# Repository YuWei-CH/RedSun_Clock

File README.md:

# RedSun_Clock
RedSun_Clock is a PCB-based clock that I designed and developed independently. The project was guided by Mr.Ethan and Mr.Matthew during the Google Hardware Product Sprint (HPS2022 Summer). 

This project consists of two main parts: Hardware and Software.

## Hardware
The hardware part includes the design of the circuit board and the bill of materials (BOM).
Essential components:
LED Matrix  
Micro-controller(atmega328)  
Quartz crystal unit  
Printed Circuit Board  

## Software
The software part is composed of code written in Arduino, which drives the operation of the hardware. And I use KiCAD for PCB design and verification.

## How to compile the code
You can use the Arduino compiler to compile this code.

## Picture

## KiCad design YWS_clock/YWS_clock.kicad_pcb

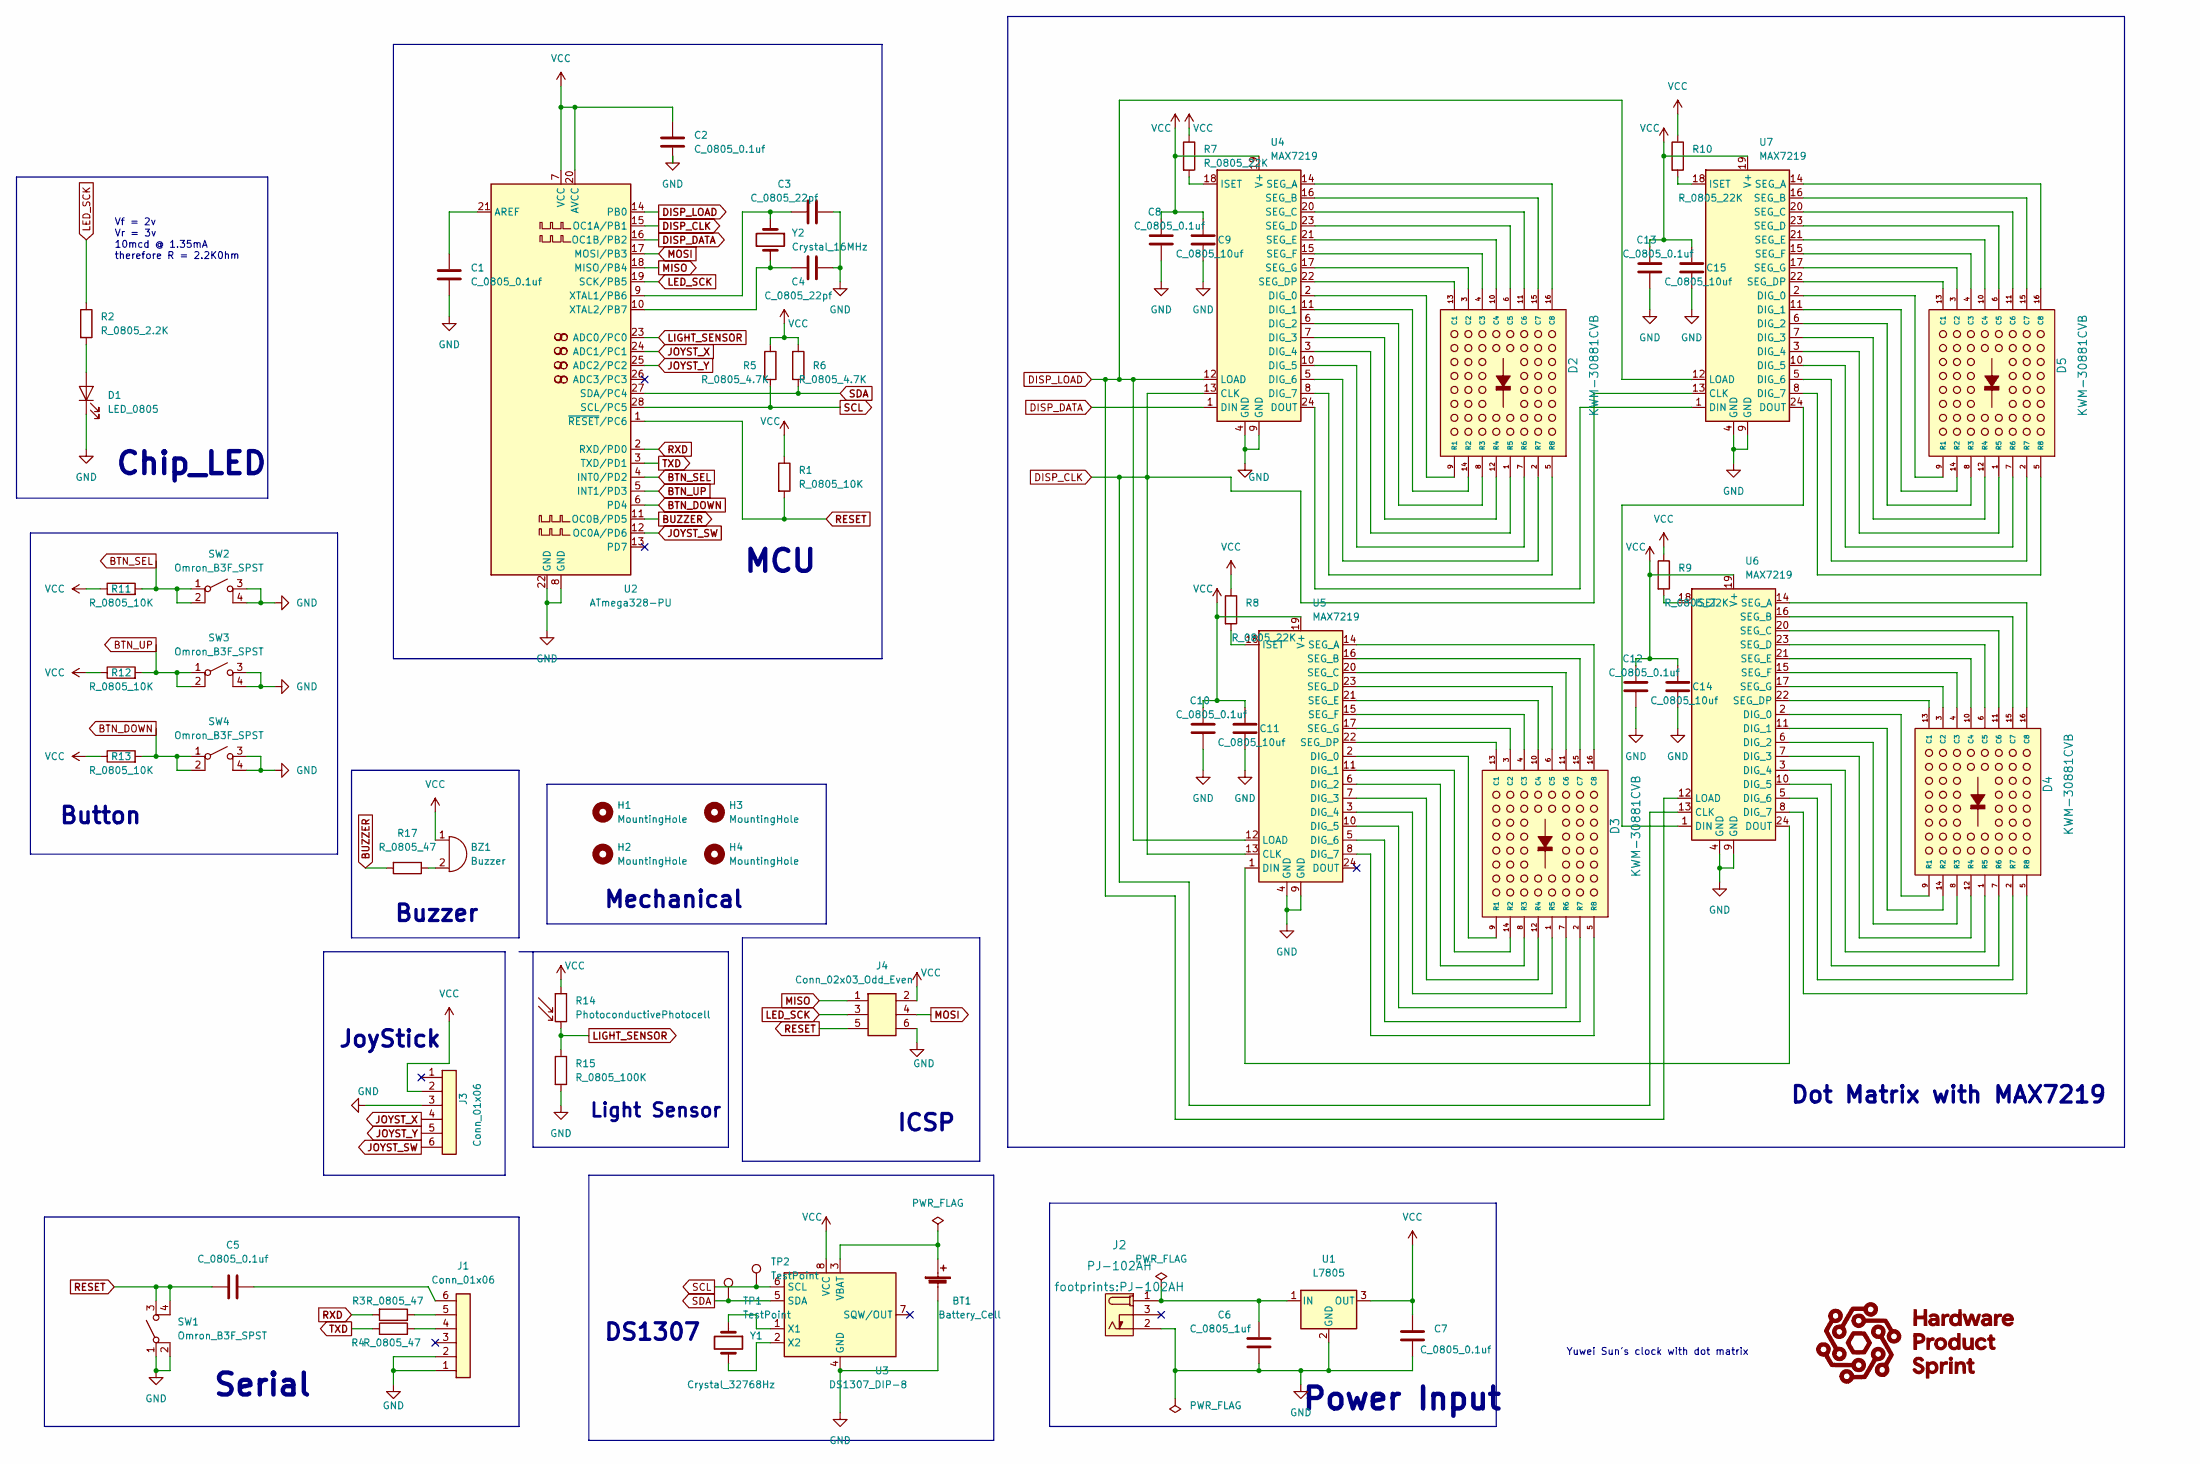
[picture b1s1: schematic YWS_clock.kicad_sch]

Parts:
BT1: Battery_Cell; BatteryHolder_Keystone_106_1x20mm; MPN BS-7; Digikey PN BS-7-ND
BZ1: Buzzer; Buzzer_TDK_PS1240P02BT_D12.2mm_H6.5mm; MPN PS1420P02CT; Digikey PN 445-2526-1-ND
C1, C2, C5, C7, C8, C10, C12, C13: C_0805_0.1uf; C_0805_2012Metric; Voltage N/A; Tolerance N/A; MPN 08055C104KAT2A; Digikey PN 478-1395-1-ND
C3, C4: C_0805_22pf; C_0805_2012Metric; Voltage N/A; Tolerance N/A; MPN CC0805JRNPO9BN220; Digikey PN 311-1103-1-ND
C6: C_0805_1uf; C_0805_2012Metric; Voltage N/A; Tolerance N/A; MPN CC0805KKX7R8BB105; Digikey PN 311-1456-1-ND
C9, C11, C14, C15: C_0805_10uf; C_0805_2012Metric; Voltage N/A; Tolerance N/A; MPN GRM21BR61E106KA73L; Digikey PN 490-5523-1-ND
D1: LED_0805; LED_0805_2012Metric; MPN 150080RS75000; Digikey PN 732-4984-1-ND
D2, D3, D4, D5: KWM-30881CVB; MPN KWM-30881CVB; Digikey PN N/A
H1, H2, H3, H4: MountingHole; MountingHole_3.2mm_M3
J1, J3: Conn_01x06; PinHeader_1x06_P2.54mm_Vertical; MPN 61300611121; Digikey PN 732-5319-ND
J2: PJ-102AH; MPN PJ-102AH; Digikey PN CP-102AH-ND
J4: Conn_02x03_Odd_Even; PinHeader_2x03_P2.54mm_Vertical; MPN PRPC003DAAN-RC; Digikey PN S2011EC-03-ND
R1, R11, R12, R13: R_0805_10K; R_0805_2012Metric; Tolerance N/A; MPN RC0805FR-0710KL; Digikey PN 311-10.0KCRCT-ND
R2: R_0805_2.2K; R_0805_2012Metric; Tolerance N/A; MPN N/A; Digikey PN 311-2.20KCRCT-ND
R3, R4, R17: R_0805_47; R_0805_2012Metric; Tolerance N/A; Mouser PN N/A; Digikey PN RC0805FR-0747RL
R5, R6: R_0805_4.7K; R_0805_2012Metric; Tolerance N/A; MPN RC0805FR-074K7L; Digikey PN 311-4.70KCRCT-ND
R7, R8, R9, R10: R_0805_22K; R_0805_2012Metric; Tolerance N/A; MPN RC0805FR-0722KL; Digikey PN 311-22.0KCRCT-ND
R14: PhotoconductivePhotocell; R_LDR_4.9x4.2mm_P2.54mm_Vertical; Voltage N/A; Tolerance N/A; MPN PDV-P8103; Digikey PN PDV-P8103-ND
R15: R_0805_100K; R_0805_2012Metric; Tolerance N/A; MPN RC0805FR-07100KL; Digikey PN 311-100KCRCT-ND
SW1, SW2, SW3, SW4: Omron_B3F_SPST; SW_SPST_Omron_B3FS-100xP; MPN B3FS-1000P; Digikey PN SW423CT-ND
TP1, TP2: TestPoint; TestPoint_THTPad_D2.0mm_Drill1.0mm
U1: L7805; TO-252-2; MPN L7805CDT-TR; Digikey PN 497-7255-1-ND
U2: ATmega328-PU; DIP-28_W7.62mm; MPN ED281DT; Digikey PN ED3050-5-ND
U3: DS1307_DIP-8; DIP-8_W7.62mm; MPN A 08-LC-TT; Digikey PN AE9986-ND
U4, U5, U6, U7: MAX7219; DIP-24_W7.62mm; MPN ED241DT; Digikey PN ED3049-5-ND
Y1: Crystal_32768Hz; Crystal_SMD_2Pin_3.2x1.5mm; MPN Q 0,032768-JTX310-12,5-20-T1-HMR-50K-LF; Digikey PN 1908-1314-1-ND
Y2: Crystal_16MHz; Crystal_SMD_HC49-SD; MPN ECS-160-20-5PXDN-TR; Digikey PN XC1299CT-ND

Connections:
BTN_DOWN: R13.2, SW4.1 (A), SW4.2 (A), U2.6 (PD4)
BTN_SEL: R11.2, SW2.1 (A), SW2.2 (A), U2.4 (INT0/PD2)
BTN_UP: R12.2, SW3.1 (A), SW3.2 (A), U2.5 (INT1/PD3)
BUZZER: R17.2, U2.11 (OC0B/PD5)
DISP_CLK: U2.15 (OC1A/PB1), U4.13 (CLK), U5.13 (CLK), U6.13 (CLK), U7.13 (CLK)
DISP_DATA: U2.16 (OC1B/PB2), U4.1 (DIN)
DISP_LOAD: U2.14 (PB0), U4.12 (LOAD), U5.12 (LOAD), U6.12 (LOAD), U7.12 (LOAD)
GND: BT1.2 (-), C1.2, C2.2, C3.2, C4.2, C6.2, C7.2, C8.2, C9.2, C10.2, C11.2, C12.2, C13.2, C14.2, C15.2, D1.1 (K), J1.1, J1.2, J2.2 (OUT), J3.3, J4.6, R15.2, SW1.1 (A), SW1.2 (A), SW2.3 (B), SW2.4 (B), SW3.3 (B), SW3.4 (B), SW4.3 (B), SW4.4 (B), U1.2 (GND), U2.8 (GND), U2.22 (GND), U3.4 (GND), U4.4 (GND), U4.9 (GND), U5.4 (GND), U5.9 (GND), U6.4 (GND), U6.9 (GND), U7.4 (GND), U7.9 (GND)
JOYST_SW: J3.6, U2.12 (OC0A/PD6)
JOYST_X: J3.4, U2.24 (ADC1/PC1)
JOYST_Y: J3.5, U2.25 (ADC2/PC2)
LED_SCK: J4.3, R2.1, U2.19 (SCK/PB5)
LIGHT_SENSOR: R14.2, R15.1, U2.23 (ADC0/PC0)
MISO: J4.1, U2.18 (MISO/PB4)
MOSI: J4.4, U2.17 (MOSI/PB3)
unnamed: BT1.1 (+), U3.3 (VBAT)
unnamed: BZ1.2 (+), R17.1
unnamed: C1.1, U2.21 (AREF)
unnamed: C3.1, U2.9 (XTAL1/PB6), Y2.1
unnamed: C4.1, U2.10 (XTAL2/PB7), Y2.2
unnamed: C5.2, J1.6
unnamed: C6.1, J2.1 (POLE), U1.1 (IN)
unnamed: D1.2 (A), R2.2
unnamed: D2.1 (R5), U4.3 (DIG_4)
unnamed: D2.2 (R7), U4.5 (DIG_6)
unnamed: D2.3 (C2), U4.17 (SEG_G)
unnamed: D2.4 (C3), U4.15 (SEG_F)
unnamed: D2.5 (R8), U4.8 (DIG_7)
unnamed: D2.6 (C5), U4.23 (SEG_D)
unnamed: D2.7 (R6), U4.10 (DIG_5)
unnamed: D2.8 (R3), U4.6 (DIG_2)
unnamed: D2.9 (R1), U4.2 (DIG_0)
unnamed: D2.10 (C4), U4.21 (SEG_E)
unnamed: D2.11 (C6), U4.20 (SEG_C)
unnamed: D2.12 (R4), U4.7 (DIG_3)
unnamed: D2.13 (C1), U4.22 (SEG_DP)
unnamed: D2.14 (R2), U4.11 (DIG_1)
unnamed: D2.15 (C7), U4.16 (SEG_B)
unnamed: D2.16 (C8), U4.14 (SEG_A)
unnamed: D3.1 (R5), U5.3 (DIG_4)
unnamed: D3.2 (R7), U5.5 (DIG_6)
unnamed: D3.3 (C2), U5.17 (SEG_G)
unnamed: D3.4 (C3), U5.15 (SEG_F)
unnamed: D3.5 (R8), U5.8 (DIG_7)
unnamed: D3.6 (C5), U5.23 (SEG_D)
unnamed: D3.7 (R6), U5.10 (DIG_5)
unnamed: D3.8 (R3), U5.6 (DIG_2)
unnamed: D3.9 (R1), U5.2 (DIG_0)
unnamed: D3.10 (C4), U5.21 (SEG_E)
unnamed: D3.11 (C6), U5.20 (SEG_C)
unnamed: D3.12 (R4), U5.7 (DIG_3)
unnamed: D3.13 (C1), U5.22 (SEG_DP)
unnamed: D3.14 (R2), U5.11 (DIG_1)
unnamed: D3.15 (C7), U5.16 (SEG_B)
unnamed: D3.16 (C8), U5.14 (SEG_A)
unnamed: D4.1 (R5), U6.3 (DIG_4)
unnamed: D4.2 (R7), U6.5 (DIG_6)
unnamed: D4.3 (C2), U6.17 (SEG_G)
unnamed: D4.4 (C3), U6.15 (SEG_F)
unnamed: D4.5 (R8), U6.8 (DIG_7)
unnamed: D4.6 (C5), U6.23 (SEG_D)
unnamed: D4.7 (R6), U6.10 (DIG_5)
unnamed: D4.8 (R3), U6.6 (DIG_2)
unnamed: D4.9 (R1), U6.2 (DIG_0)
unnamed: D4.10 (C4), U6.21 (SEG_E)
unnamed: D4.11 (C6), U6.20 (SEG_C)
unnamed: D4.12 (R4), U6.7 (DIG_3)
unnamed: D4.13 (C1), U6.22 (SEG_DP)
unnamed: D4.14 (R2), U6.11 (DIG_1)
unnamed: D4.15 (C7), U6.16 (SEG_B)
unnamed: D4.16 (C8), U6.14 (SEG_A)
unnamed: D5.1 (R5), U7.3 (DIG_4)
unnamed: D5.2 (R7), U7.5 (DIG_6)
unnamed: D5.3 (C2), U7.17 (SEG_G)
unnamed: D5.4 (C3), U7.15 (SEG_F)
unnamed: D5.5 (R8), U7.8 (DIG_7)
unnamed: D5.6 (C5), U7.23 (SEG_D)
unnamed: D5.7 (R6), U7.10 (DIG_5)
unnamed: D5.8 (R3), U7.6 (DIG_2)
unnamed: D5.9 (R1), U7.2 (DIG_0)
unnamed: D5.10 (C4), U7.21 (SEG_E)
unnamed: D5.11 (C6), U7.20 (SEG_C)
unnamed: D5.12 (R4), U7.7 (DIG_3)
unnamed: D5.13 (C1), U7.22 (SEG_DP)
unnamed: D5.14 (R2), U7.11 (DIG_1)
unnamed: D5.15 (C7), U7.16 (SEG_B)
unnamed: D5.16 (C8), U7.14 (SEG_A)
unnamed: J1.4, R4.2
unnamed: J1.5, R3.1
unnamed: R7.2, U4.18 (ISET)
unnamed: R8.2, U5.18 (ISET)
unnamed: R9.2, U6.18 (ISET)
unnamed: R10.2, U7.18 (ISET)
unnamed: U3.1 (X1), Y1.1
unnamed: U3.2 (X2), Y1.2
unnamed: U4.24 (DOUT), U7.1 (DIN)
unnamed: U5.1 (DIN), U6.24 (DOUT)
unnamed: U6.1 (DIN), U7.24 (DOUT)
RESET: C5.1, J4.5, R1.2, SW1.3 (B), SW1.4 (B), U2.1 (~RESET/PC6)
RXD: R3.2, U2.2 (RXD/PD0)
SCL: R5.2, TP2.1, U2.28 (SCL/PC5), U3.6 (SCL)
SDA: R6.2, TP1.1, U2.27 (SDA/PC4), U3.5 (SDA)
TXD: R4.1, U2.3 (TXD/PD1)
VCC: BZ1.1 (-), C2.1, C7.1, C8.1, C9.1, C10.1, C11.1, C12.1, C13.1, C14.1, C15.1, J3.2, J4.2, R1.1, R5.1, R6.1, R7.1, R8.1, R9.1, R10.1, R11.1, R12.1, R13.1, R14.1, U1.3 (OUT), U2.7 (VCC), U2.20 (AVCC), U3.8 (VCC), U4.19 (V+), U5.19 (V+), U6.19 (V+), U7.19 (V+)

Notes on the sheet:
MCU
JoyStick
ICSP
Serial
Power Input
Chip_LED
Buzzer
Yuwei Sun's clock with dot matrix
Vf = 2v Vr = 3v 10mcd @ 1.35mA therefore R = 2.2K0hm
Light Sensor
Dot Matrix with MAX7219
DS1307
Button
Mechanical

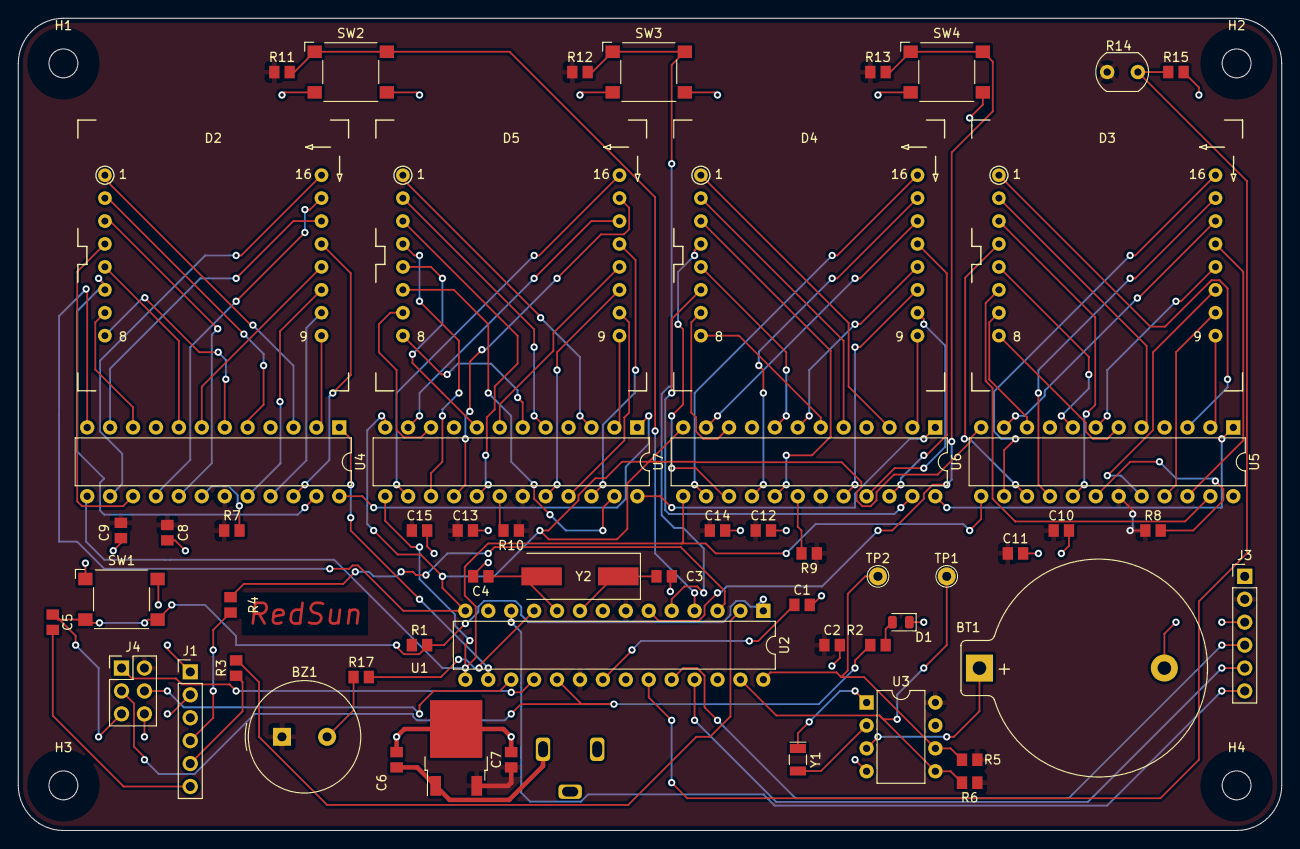
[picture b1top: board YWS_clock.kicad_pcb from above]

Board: 2 copper layers, 140.0 x 90.0 mm, 61 parts (1 on the bottom side), 104 nets.

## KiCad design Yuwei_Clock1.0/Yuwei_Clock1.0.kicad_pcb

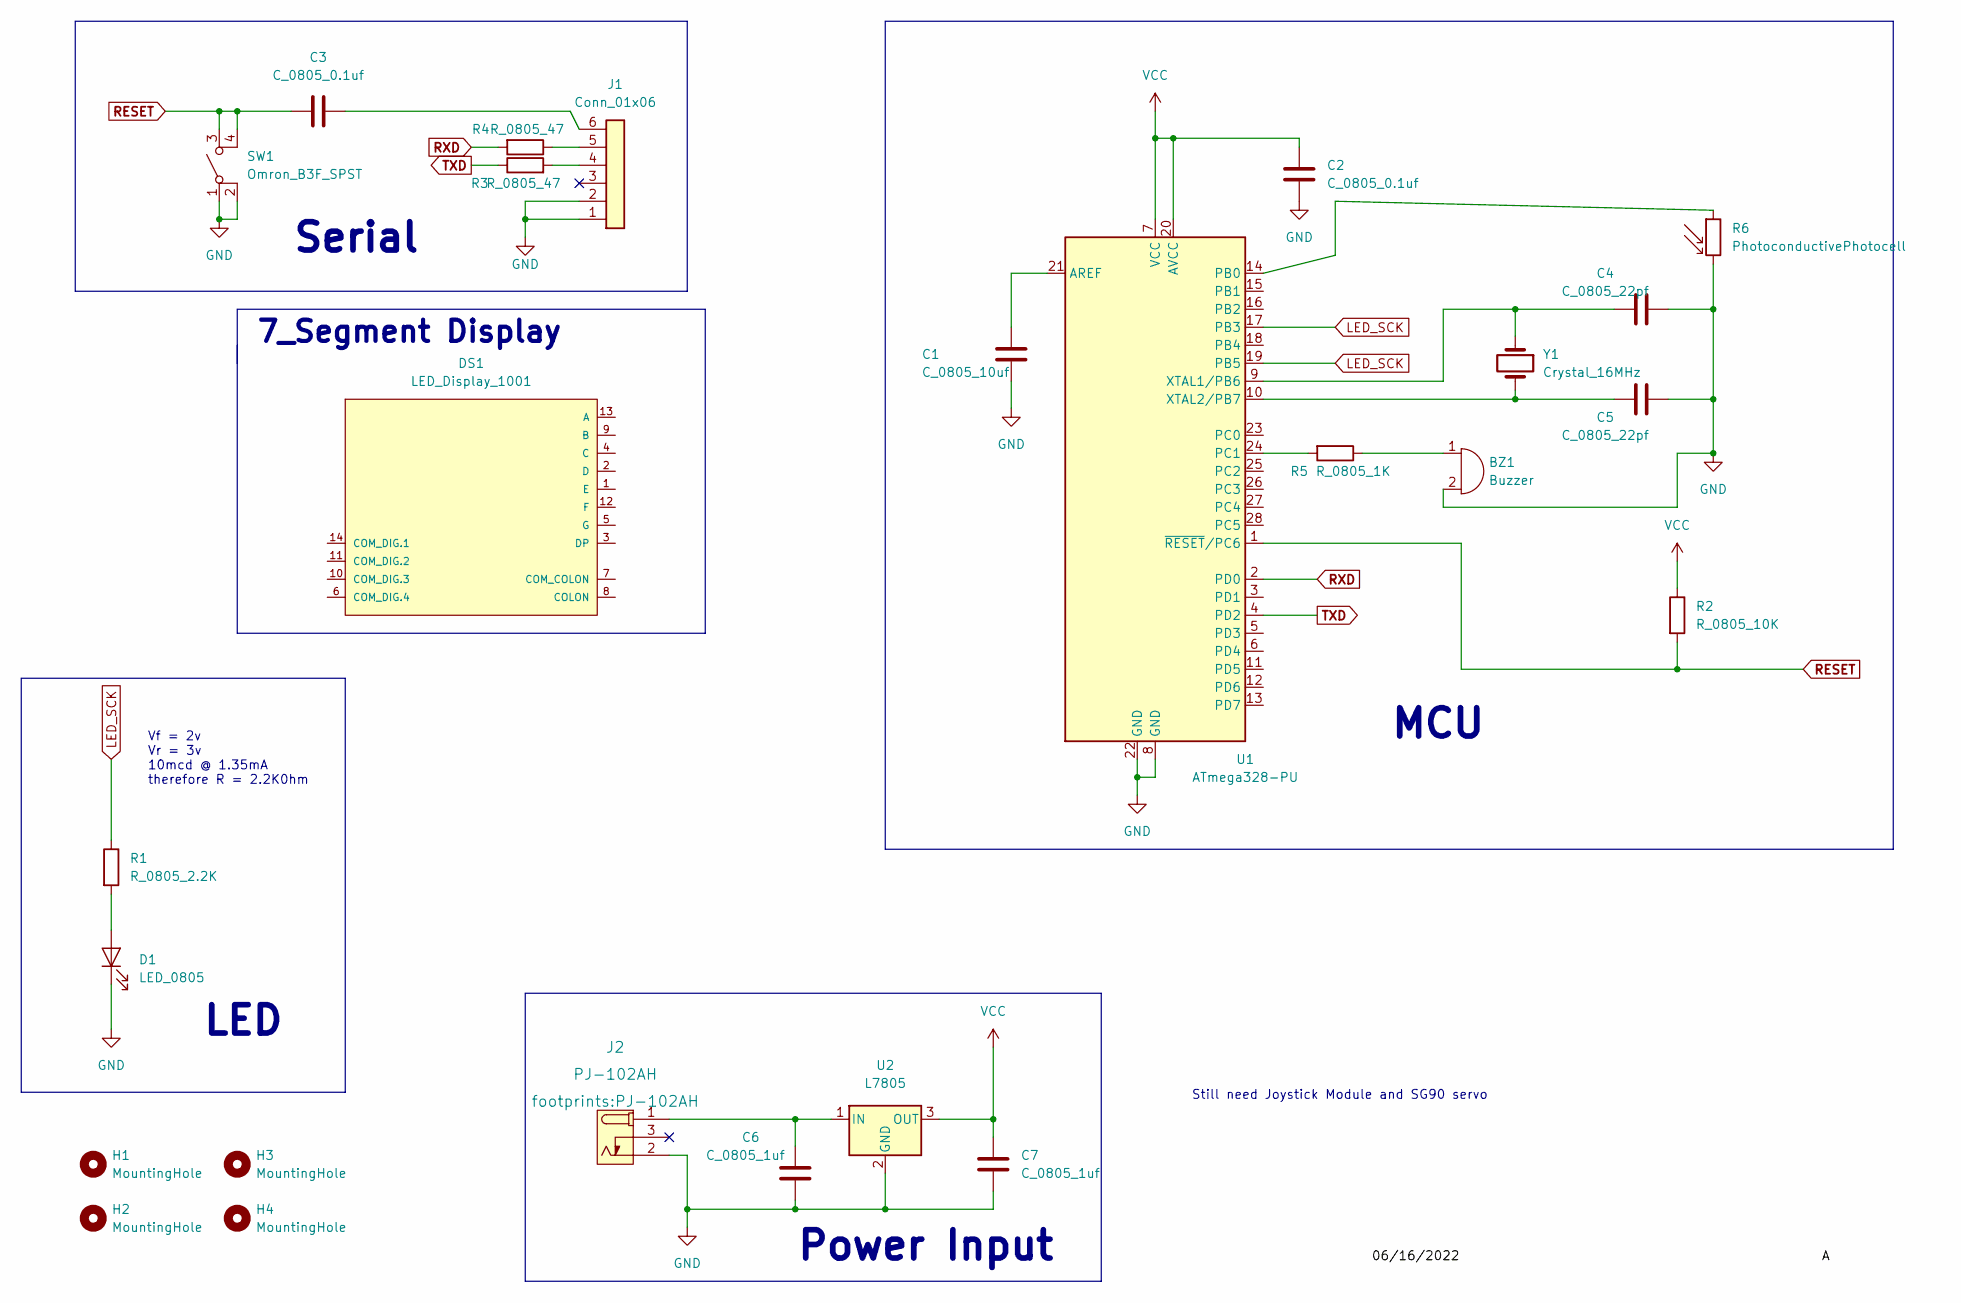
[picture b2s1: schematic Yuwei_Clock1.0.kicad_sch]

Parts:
BZ1: Buzzer; Buzzer_TDK_PS1240P02BT_D12.2mm_H6.5mm; MPN PS1420P02CT; Digikey PN 445-2526-1-ND
C1: C_0805_10uf; C_0805_2012Metric; Voltage N/A; Tolerance N/A; MPN GRM21BR61E106KA73L; Digikey PN 490-5523-1-ND
C2, C3: C_0805_0.1uf; C_0805_2012Metric; Voltage N/A; Tolerance N/A; MPN 08055C104KAT2A; Digikey PN 478-1395-1-ND
C4, C5: C_0805_22pf; C_0805_2012Metric; Voltage N/A; Tolerance N/A; MPN CC0805JRNPO9BN220; Digikey PN 311-1103-1-ND
C6, C7: C_0805_1uf; C_0805_2012Metric; Voltage N/A; Tolerance N/A; MPN CC0805KKX7R8BB105; Digikey PN 311-1456-1-ND
D1: LED_0805; LED_0805_2012Metric; MPN 150080RS75000; Digikey PN 732-4984-1-ND
DS1: LED_Display_1001; Adafruit-1001-0-0-MFG; forward voltage 3.2V; reverse voltage 5V; mouser part number 485-1001; digikey description WHITE 7-SEGMENT CLOCK DISPLAY
H1, H2, H3, H4: MountingHole; MountingHole_3.2mm_M3
J1: Conn_01x06; PinHeader_1x06_P2.54mm_Vertical; MPN 61300611121; Digikey PN 732-5319-ND
J2: PJ-102AH; MPN PJ-102AH; Digikey PN CP-102AH-ND
R1: R_0805_2.2K; R_0805_2012Metric; Tolerance N/A; MPN N/A; Digikey PN 311-2.20KCRCT-ND
R2: R_0805_10K; R_0805_2012Metric; Tolerance N/A; MPN RC0805FR-0710KL; Digikey PN 311-10.0KCRCT-ND
R3, R4: R_0805_47; R_0805_2012Metric; Tolerance N/A; Mouser PN N/A; Digikey PN RC0805FR-0747RL
R5: R_0805_1K; R_0805_2012Metric; Tolerance N/A; Mouser PN N/A; Digikey PN RC0805FR-0710KL
R6: PhotoconductivePhotocell; R_LDR_4.9x4.2mm_P2.54mm_Vertical; Voltage N/A; Tolerance N/A; MPN PDV-P8103; Digikey PN PDV-P8103-ND
SW1: Omron_B3F_SPST; SW_SPST_Omron_B3FS-100xP; MPN B3FS-1000P; Digikey PN SW423CT-ND
U1: ATmega328-PU; DIP-28_W7.62mm; MPN ED281DT; Digikey PN ED3050-5-ND
U2: L7805; TO-220-3_Horizontal_TabDown
Y1: Crystal_16MHz; Crystal_SMD_HC49-SD; MPN ECS-160-20-5PXDN-TR; Digikey PN XC1299CT-ND

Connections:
GND: BZ1.2 (+), C1.2, C2.2, C4.2, C5.2, C6.2, C7.2, D1.1 (K), J1.1, J1.2, J2.2 (OUT), R6.2, SW1.1 (A), SW1.2 (A), U1.8 (GND), U1.22 (GND), U2.2 (GND); also elsewhere on the board
LED_SCK: R1.1, U1.17 (PB3), U1.19 (PB5)
unnamed: BZ1.1 (-), R5.1
unnamed: C1.1, U1.21 (AREF)
unnamed: C3.2, J1.6
unnamed: C4.1, U1.9 (XTAL1/PB6), Y1.1
unnamed: C5.1, U1.10 (XTAL2/PB7), Y1.2
unnamed: C6.1, J2.1 (POLE), U2.1 (IN)
unnamed: D1.2 (A), R1.2
unnamed: J1.4, R3.2
unnamed: J1.5, R4.1
unnamed: R6.1, U1.14 (PB0)
unnamed: R5.2, U1.24 (PC1)
RESET: C3.1, R2.2, SW1.3 (B), SW1.4 (B), U1.1 (~RESET/PC6)
RXD: R4.2, U1.2 (PD0)
TXD: R3.1, U1.4 (PD2)
VCC: C2.1, C7.1, R2.1, U1.7 (VCC), U1.20 (AVCC), U2.3 (OUT)

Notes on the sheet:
Still need Joystick Module and SG90 servo
Vf = 2v Vr = 3v 10mcd @ 1.35mA therefore R = 2.2K0hm
MCU
Serial
7_Segment Display
Power Input
LED

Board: 2 copper layers, 27 parts (0 on the bottom side), 17 nets, no tracks yet.

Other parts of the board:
J?: Conn_01x06; PinHeader_1x06_P2.54mm_Vertical

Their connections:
GND: J?.1, J?.2; also elsewhere on the board

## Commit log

2022-06-03 My first design comment
2022-06-12 design for week 1
2022-06-12 LED blink
2022-06-12 New schematic of week 1
2022-06-12 Change polar capacitor to C_0805_10uf
2022-06-15 Update with Arduino Button function
    When button pressed, serial will display string.
2022-06-17 Update with Schematic and PCB
2022-06-25 Update with RTC
2022-06-29 dot matrix version
2022-06-30 Update matrix dot
2022-07-01 Update Buzzer and joystick
2022-07-01 update PCB and Schematic with dot matrix
2022-07-01 Update button
2022-07-02 Update with PCB layout
2022-07-02 update with supplementary material and dot matrix display code
2022-07-07 Add ICSP and separate sections
2022-07-17 Initial version with full routing and test point
2022-07-17 Update with gerbers and BOM
2022-07-17 Update with STEP file
2022-07-22 live review update
2022-07-22 update with modified PCB
2022-07-22 Final version for final review
2022-07-22 3 error fixed
2022-07-22 update with gerber, BOM, drill
2022-07-22 flip the power init
2022-07-22 update with 1.0_version zip
2022-08-14 Update with Code and file separations
2022-08-15 Update with test code and delete HPS lib
2022-09-01 Update with debug code
2022-09-01 Update User Doc
